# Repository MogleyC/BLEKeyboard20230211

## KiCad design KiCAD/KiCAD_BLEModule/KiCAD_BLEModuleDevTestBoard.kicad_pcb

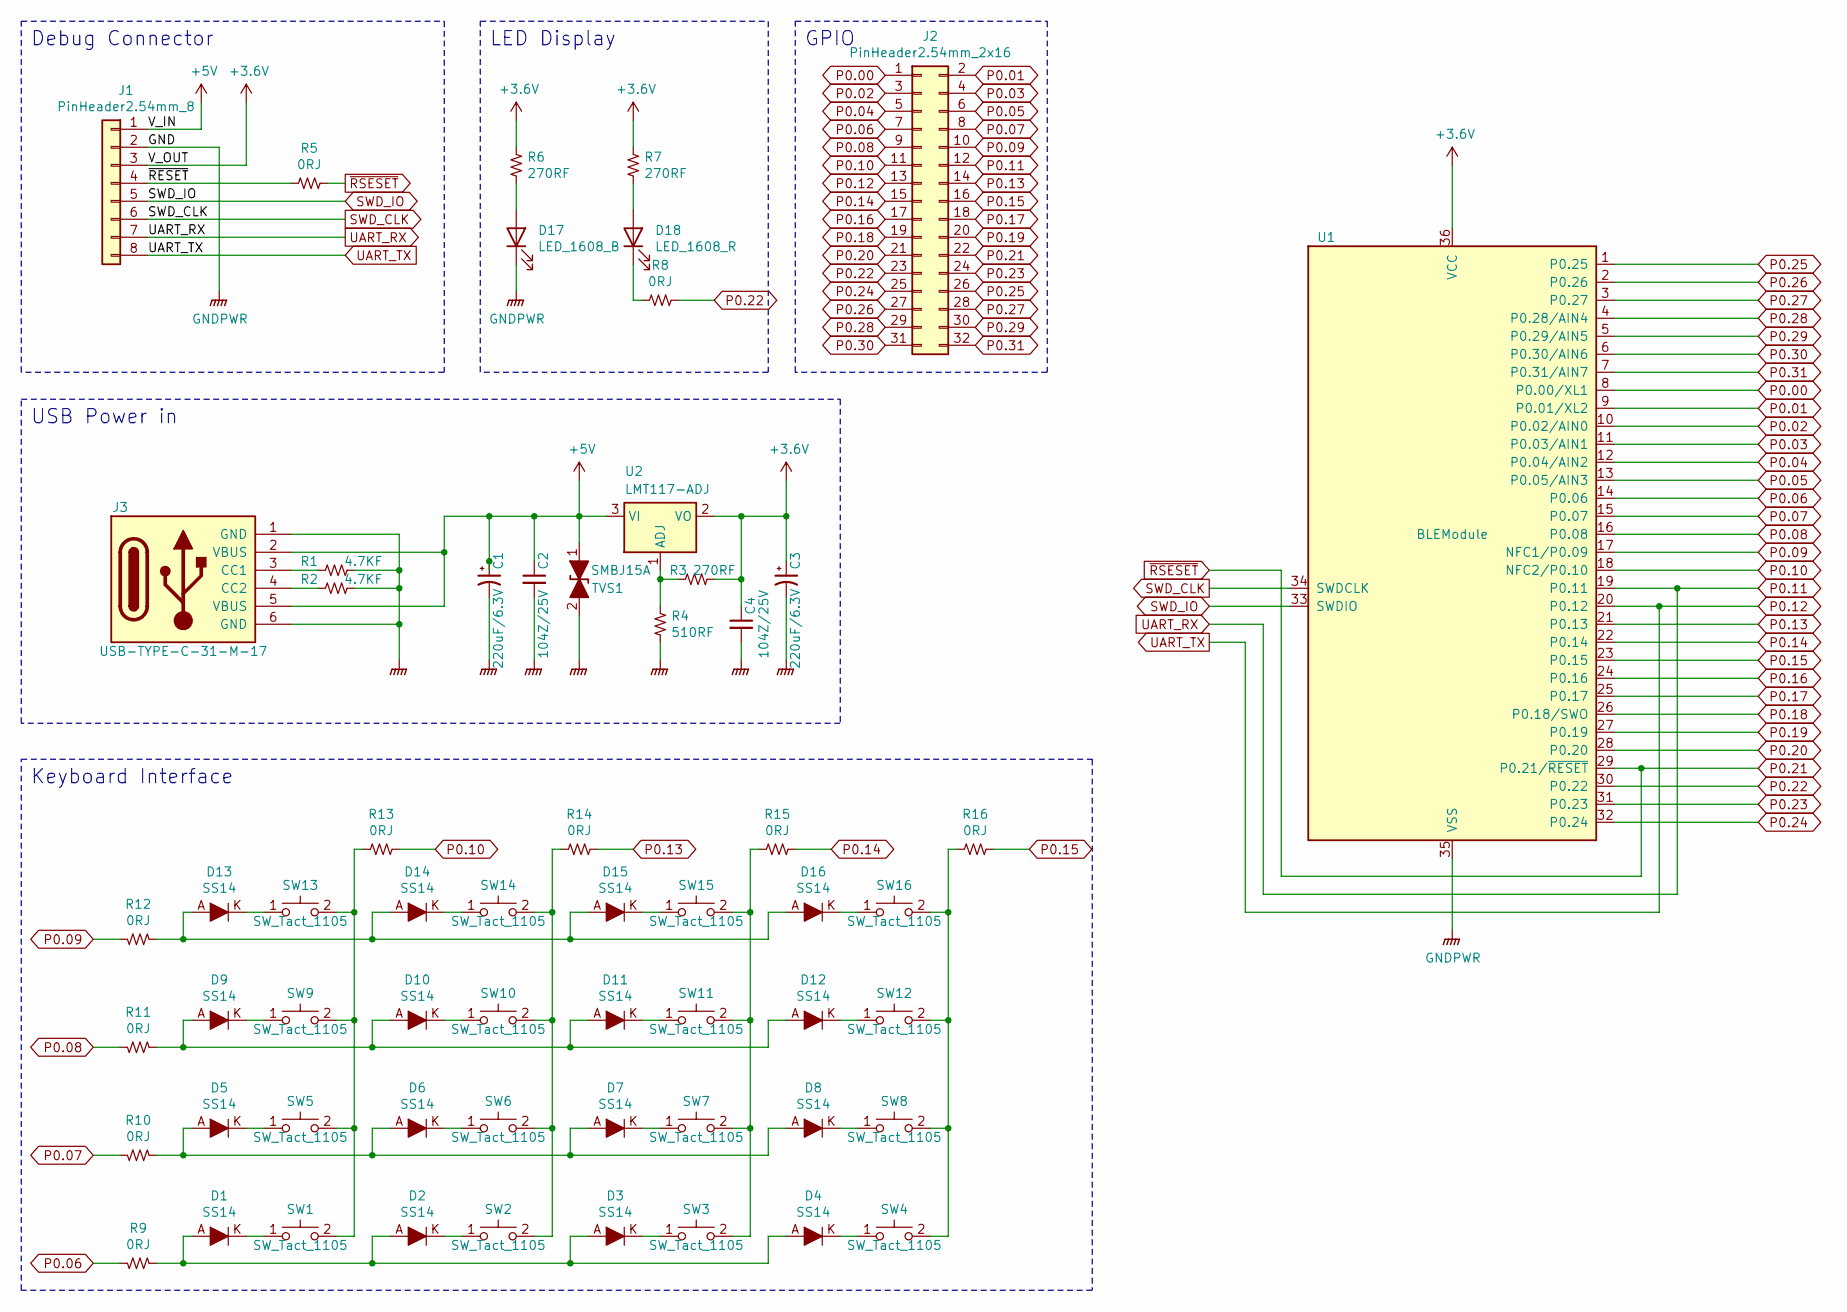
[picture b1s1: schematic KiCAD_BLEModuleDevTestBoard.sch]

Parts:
C1, C3: CAP_220uF_6.3V_SC6.3X5.8; C_Elec_6.3x5.8; PartName 220uF/6.3V
C2, C4: CAP_104Z_25V_1608; C_0603_1608Metric; PartName 104Z/25V
D1, D2, D3, D4, D5, D6, D7, D8, D9, D10, D11, D12, D13, D14, D15, D16: SS14; DO-214AC
D17: LED_1608_B; LED_0603_1608Metric
D18: LED_1608_R; LED_0603_1608Metric
J1: PinHeader2.54mm_8; PinHeader_1x08_P2.54mm_Vertical; PartName PinHeader2.54mm-8P
J2: PinHeader2.54mm_2x16; PinSocket_2x16_P2.54mm_Vertical
J3: USB-TYPE-C-31-M-17; TYPE-C-31-M-17-1; PartName USB-TYPE-C-31-M-17
R1, R2: R_4.7KF; R_0603_1608Metric; PartName 4.7KF
R3, R6, R7: R_270RF; R_0603_1608Metric; PartName 270RF
R4: R_510RF; R_0603_1608Metric; PartName 510RF
R5, R8, R9, R10, R11, R12, R13, R14, R15, R16: R_0RJ; R_0603_1608Metric; PartName 0RJ
SW1, SW2, SW3, SW4, SW5, SW6, SW7, SW8, SW9, SW10, SW11, SW12, SW13, SW14, SW15, SW16: SW_Tact_1105; SW_PUSH_6mm_H5mm; PartName ITS-1105-5mm
TVS1: SMBJ15A; D_SMB; PartName SMBJ15A
U1: BLEModule
U2: LMT117-ADJ; SOT-223-3_TabPin2; PartName LMT117-ADJ

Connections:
+3.6V: C3.1, C4.1, J1.3, R3.1, R6.1, R7.1, U1.36 (VCC), U2.2 (VO)
+5V: C1.1, C2.1, J1.1, J3.2 (VBUS), J3.5 (VBUS), TVS1.1 (A1), U2.3 (VI)
/~RESET: J1.4, R5.2
GNDPWR: C1.2, C2.2, C3.2, C4.2, D17.1 (K), J1.2, J3.1 (GND), J3.6 (GND), R1.1, R2.1, R4.2, TVS1.2 (A2), U1.35 (VSS)
unnamed: D1.A, D2.A, D3.A, D4.A, R9.2
unnamed: D1.K, SW1.1
unnamed: D2.K, SW2.1
unnamed: D3.K, SW3.1
unnamed: D4.K, SW4.1
unnamed: D5.A, D6.A, D7.A, D8.A, R10.2
unnamed: D5.K, SW5.1
unnamed: D6.K, SW6.1
unnamed: D7.K, SW7.1
unnamed: D8.K, SW8.1
unnamed: D9.K, SW9.1
unnamed: D9.A, D10.A, D11.A, D12.A, R11.2
unnamed: D10.K, SW10.1
unnamed: D11.K, SW11.1
unnamed: D12.K, SW12.1
unnamed: D13.A, D14.A, D15.A, D16.A, R12.2
unnamed: D13.K, SW13.1
unnamed: D14.K, SW14.1
unnamed: D15.K, SW15.1
unnamed: D16.K, SW16.1
unnamed: D17.2 (A), R6.2
unnamed: D18.1 (K), R8.2
unnamed: D18.2 (A), R7.2
unnamed: J3.3 (CC1), R1.2
unnamed: J3.4 (CC2), R2.2
unnamed: R3.2, R4.1, U2.1 (ADJ)
unnamed: R13.2, SW1.2, SW5.2, SW9.2, SW13.2
unnamed: R14.2, SW2.2, SW6.2, SW10.2, SW14.2
unnamed: R15.2, SW3.2, SW7.2, SW11.2, SW15.2
unnamed: R16.2, SW4.2, SW8.2, SW12.2, SW16.2
P0.00: J2.1, U1.8 (P0.00/XL1)
P0.01: J2.2, U1.9 (P0.01/XL2)
P0.02: J2.3, U1.10 (P0.02/AIN0)
P0.03: J2.4, U1.11 (P0.03/AIN1)
P0.04: J2.5, U1.12 (P0.04/AIN2)
P0.05: J2.6, U1.13 (P0.05/AIN3)
P0.06: J2.7, R9.1, U1.14 (P0.06)
P0.07: J2.8, R10.1, U1.15 (P0.07)
P0.08: J2.9, R11.1, U1.16 (P0.08)
P0.09: J2.10, R12.1, U1.17 (NFC1/P0.09)
P0.10: J2.11, R13.1, U1.18 (NFC2/P0.10)
P0.11: J1.7, J2.12, U1.19 (P0.11)
P0.12: J1.8, J2.13, U1.20 (P0.12)
P0.13: J2.14, R14.1, U1.21 (P0.13)
P0.14: J2.15, R15.1, U1.22 (P0.14)
P0.15: J2.16, R16.1, U1.23 (P0.15)
P0.16: J2.17, U1.24 (P0.16)
P0.17: J2.18, U1.25 (P0.17)
P0.18: J2.19, U1.26 (P0.18/SWO)
P0.19: J2.20, U1.27 (P0.19)
P0.20: J2.21, U1.28 (P0.20)
P0.21: J2.22, R5.1, U1.29 (P0.21/~RESET)
P0.22: J2.23, R8.1, U1.30 (P0.22)
P0.23: J2.24, U1.31 (P0.23)
P0.24: J2.25, U1.32 (P0.24)
P0.25: J2.26, U1.1 (P0.25)
P0.26: J2.27, U1.2 (P0.26)
P0.27: J2.28, U1.3 (P0.27)
P0.28: J2.29, U1.4 (P0.28/AIN4)
P0.29: J2.30, U1.5 (P0.29/AIN5)
P0.30: J2.31, U1.6 (P0.30/AIN6)
P0.31: J2.32, U1.7 (P0.31/AIN7)
SWD_CLK: J1.6, U1.34 (SWDCLK)
SWD_IO: J1.5, U1.33 (SWDIO)

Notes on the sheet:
Debug Connector
GPIO
LED Display
USB Power in
Keyboard Interface

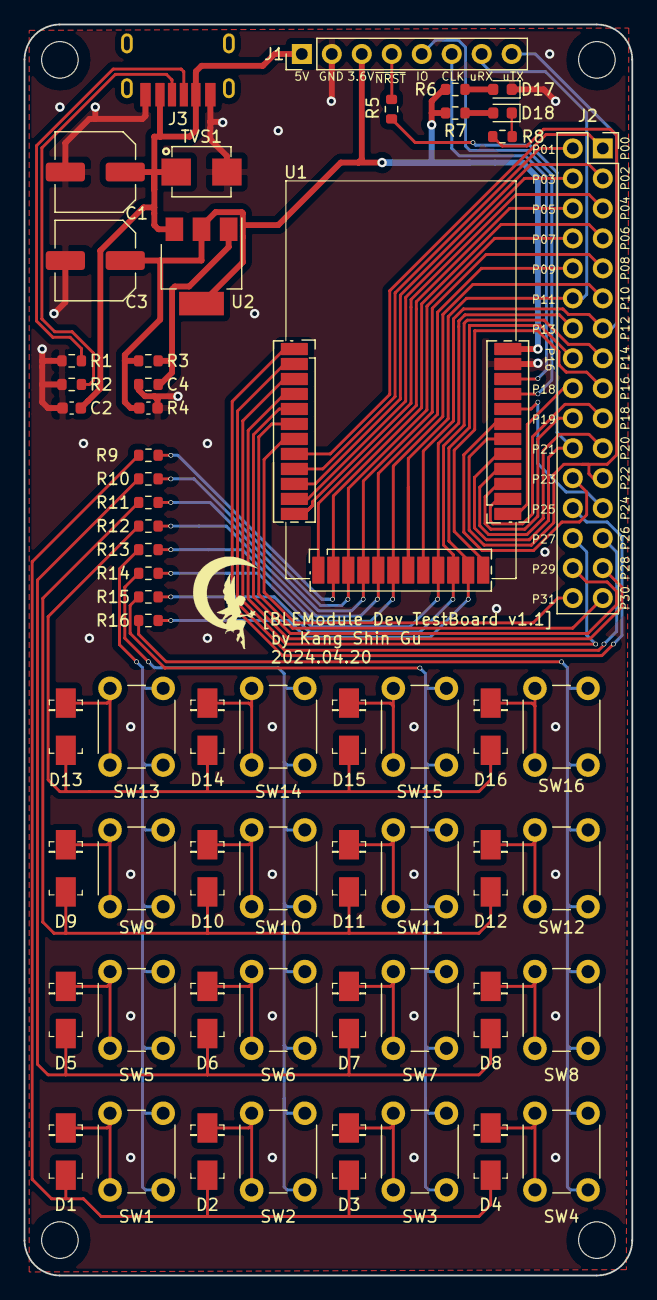
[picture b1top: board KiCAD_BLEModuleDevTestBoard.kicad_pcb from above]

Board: 2 copper layers, 51.5 x 106.0 mm, 60 parts (0 on the bottom side), 68 nets.

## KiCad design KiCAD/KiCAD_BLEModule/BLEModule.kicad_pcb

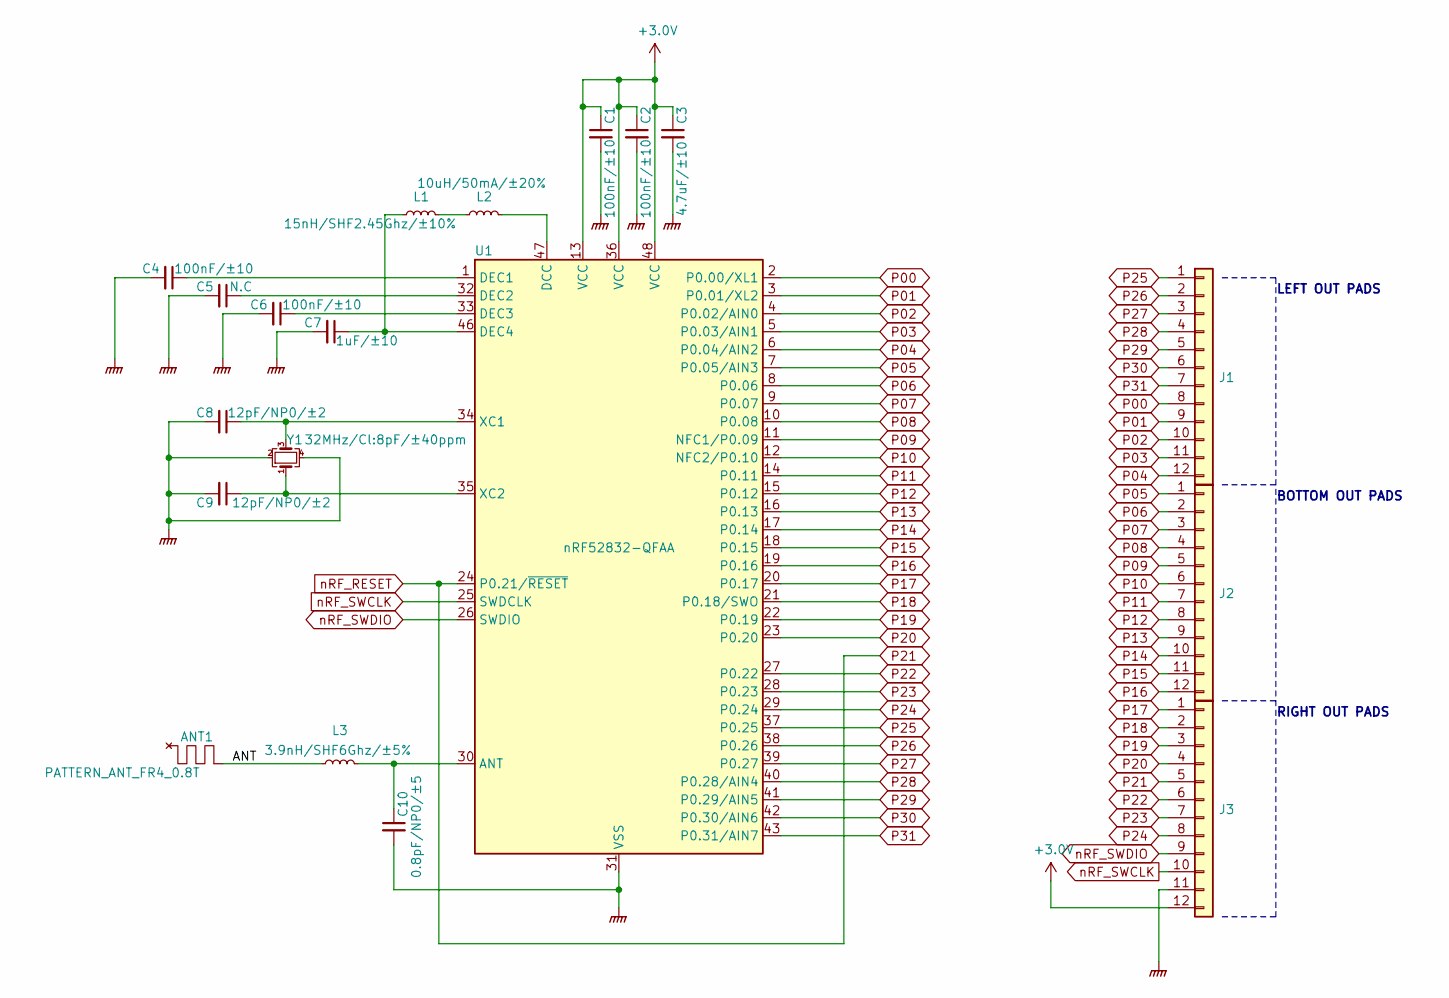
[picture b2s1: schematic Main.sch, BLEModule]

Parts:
ANT1: PATTERN_ANT_FR4_0.8T; ANT_PATTERN_FR4_0.8T
C1, C2, C4, C6: CAP_100nF_1005; C_0402_1005Metric; PartName 100nF/±10
C3: CAP_4.7uF_1005; C_0402_1005Metric; PartName 4.7uF/±10
C5: CAP_N.C_1005; C_0402_1005Metric; PartName N.C
C7: CAP_1uF_1005; C_0402_1005Metric; PartName 1uF/±10
C8, C9: CAP_12pF_1005; C_0402_1005Metric; PartName 12pF/NP0/±2
C10: CAP_0.8pF_1005; C_0402_1005Metric; PartName 0.8pF/NP0/±5
J1, J2, J3: CastellatedPinHeader1.27mm_12; CastellatedPinHeader_1x12_P1.27mm_VerticalR
L1: L_15nH; L_0402_1005Metric; PartName 15nH/SHF2.45Ghz/±10%
L2: L_10uH; L_0603_1608Metric; PartName 10uH/50mA/±20%
L3: L_3.9nH; L_0402_1005Metric; PartName 3.9nH/SHF6Ghz/±5%
U1: nRF52832-QFAA; QFN-48-1EP_6x6mm_P0.4mm_EP4.3x4.3mm; PartName nRF52832-QFAA
Y1: Y_32MHz; Crystal_SMD_2016-4Pin_2.0x1.6mm; PartName 32MHz/Cl:8pF/±40ppm

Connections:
+30V: C1.1, C2.1, C3.1, J3.12, U1.13 (VCC), U1.36 (VCC), U1.48 (VCC)
/Main/ANT: ANT1.1, L3.1
GNDPWR: C1.2, C2.2, C3.2, C4.2, C5.2, C6.2, C7.2, C8.2, C9.2, C10.2, J3.11, U1.31 (VSS), U1.45 (VSS), U1.49 (VSS), Y1.2, Y1.4
unnamed: C4.1, U1.1 (DEC1)
unnamed: C5.1, U1.32 (DEC2)
unnamed: C6.1, U1.33 (DEC3)
unnamed: C7.1, L1.1, U1.46 (DEC4)
unnamed: C8.1, U1.34 (XC1), Y1.3
unnamed: C9.1, U1.35 (XC2), Y1.1
unnamed: C10.1, L3.2, U1.30 (ANT)
unnamed: L1.2, L2.1
unnamed: L2.2, U1.47 (DCC)
P00: J1.8, U1.2 (P0.00/XL1)
P01: J1.9, U1.3 (P0.01/XL2)
P02: J1.10, U1.4 (P0.02/AIN0)
P03: J1.11, U1.5 (P0.03/AIN1)
P04: J1.12, U1.6 (P0.04/AIN2)
P05: J2.1, U1.7 (P0.05/AIN3)
P06: J2.2, U1.8 (P0.06)
P07: J2.3, U1.9 (P0.07)
P08: J2.4, U1.10 (P0.08)
P09: J2.5, U1.11 (NFC1/P0.09)
P10: J2.6, U1.12 (NFC2/P0.10)
P11: J2.7, U1.14 (P0.11)
P12: J2.8, U1.15 (P0.12)
P13: J2.9, U1.16 (P0.13)
P14: J2.10, U1.17 (P0.14)
P15: J2.11, U1.18 (P0.15)
P16: J2.12, U1.19 (P0.16)
P17: J3.1, U1.20 (P0.17)
P18: J3.2, U1.21 (P0.18/SWO)
P19: J3.3, U1.22 (P0.19)
P20: J3.4, U1.23 (P0.20)
P21: J3.5, U1.24 (P0.21/~RESET)
P22: J3.6, U1.27 (P0.22)
P23: J3.7, U1.28 (P0.23)
P24: J3.8, U1.29 (P0.24)
P25: J1.1, U1.37 (P0.25)
P26: J1.2, U1.38 (P0.26)
P27: J1.3, U1.39 (P0.27)
P28: J1.4, U1.40 (P0.28/AIN4)
P29: J1.5, U1.41 (P0.29/AIN5)
P30: J1.6, U1.42 (P0.30/AIN6)
P31: J1.7, U1.43 (P0.31/AIN7)
nRF_SWCLK: J3.10, U1.25 (SWDCLK)
nRF_SWDIO: J3.9, U1.26 (SWDIO)

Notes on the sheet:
LEFT OUT PADS
BOTTOM OUT PADS
RIGHT OUT PADS

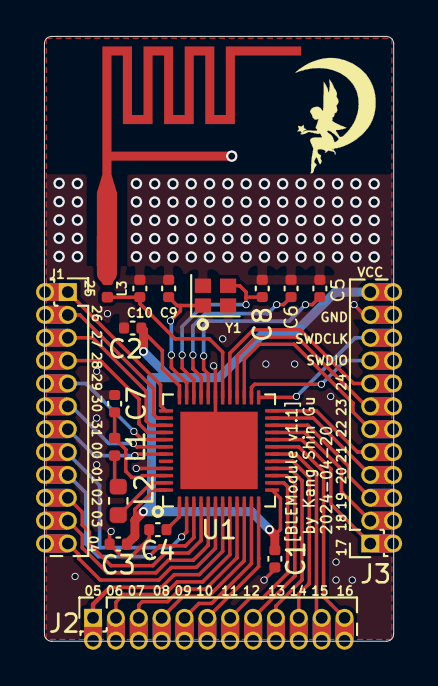
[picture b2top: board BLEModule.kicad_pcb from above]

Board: 2 copper layers, 19.4 x 33.6 mm, 19 parts (0 on the bottom side), 46 nets.

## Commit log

2023-02-26 KSG : 기본 파일 업로드 (ignore, 라이선스 등)
2023-02-26 KSG : 블루투스 레퍼런스 자료 및 Util 업로드
2023-02-26 KSG : nRF5 SDK 및 SES 설정값 업로드
2023-03-12 KSG : 신규 프로젝트 생성(nRF52832/s132형태) - 비어있는 깨끗한 빌드. 빌드 시 성공.
2023-03-12 KSG : 클린빌드 설정 중 미진한 부분 재조정(해당 버전이 진짜 클린 빌드)
2023-03-12 KSG : 기본 요소 구성중
2024-03-30 KSG : 졸업과제용 BLE 모듈 제작(주문 완료)
2024-04-06 KSG : BLE 모듈 개발용 테스트 보드 (키보드레이아웃) 아트워크 완료
2024-04-06 KSG : BLE모듈 레이아웃에 에 라운드 추가
2024-04-06 KSG : 거버파일 생성 & 잘못된 다이오드 정보 수정
2024-04-19 KSG : 아트워크 프린트 오기 수정
2024-04-20 KSG : 불필요 파일 제거
2024-04-20 KSG : 제퍼 빌드 환경 구성 완료 LED블링크 + RTT 터미널 테스트 빌드 제작
2024-04-20 KSG : 테스트 코드 수정
2024-04-20 KSG : 키보드 입력 프로토타입 테스트 완료
2024-04-21 KSG : GPIO update를 Thread형태로 변경
2024-05-18 KSG : BLE HID GATT 브로드캐스팅 셋팅(검색 테스트 확인)
2024-05-19 KSG : 인증모드로 변경. 연결끊김 후 ReAdvertising 기능 활성화.
2024-05-25 KSG : GPIO에서 Ble로 Key값 상태 MSG 송/수신 로직 추가
2024-05-25 KSG : 키 입력시 BLE HID 키송출("123456") 테스트 예제 제작
2024-05-25 KSG : 프로필 2개 제작 시작 - 프로필 형태로 구조 변경
2024-05-25 KSG : 프로필 2개 제작 시작 - 프로필 2개 적용 완료. 키 발송 테스트 완료.
2024-05-26 KSG : 다중키 입력 기반 마련(다중키 검증로직 개선 필요->기존키 비교 삭제/추가)
2024-05-26 KSG : 다중키 입력 로직 개선(검증용 링큐버퍼 적용)
2024-05-26 KSG : 구조 개선 - 공통함수를 하나로 묶음
2024-05-26 KSG : Connect, NumLock 상태 LED 표출 적용
2024-05-26 KSG : 불필요 주석 코드 삭제
2024-05-26 KSG : 크래시 안정화 (GPIO 변경후 대기시간이 짧음으로 인해 발생으로 보임)
2024-06-06 KSG : 레포트 맵에서 키보드 입력 사이즈(최대 입력 키 개수) 수정 (6->8)
